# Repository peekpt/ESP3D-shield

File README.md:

## ESP3D-SHIELD
ESP3D - it's a software based on ESP8266 module to give Wi-Fi capabilities 3D Printers.

ESP3D-SHIELD - it's an adapter to connect a 3D printer AUX-1 port

--

*ESP3D info:*

* [ESP3D](https://github.com/luc-github/ESP3D)

* [ESP3D WEBUI](https://github.com/luc-github/ESP3D-WEBUI)

--

*WIP*

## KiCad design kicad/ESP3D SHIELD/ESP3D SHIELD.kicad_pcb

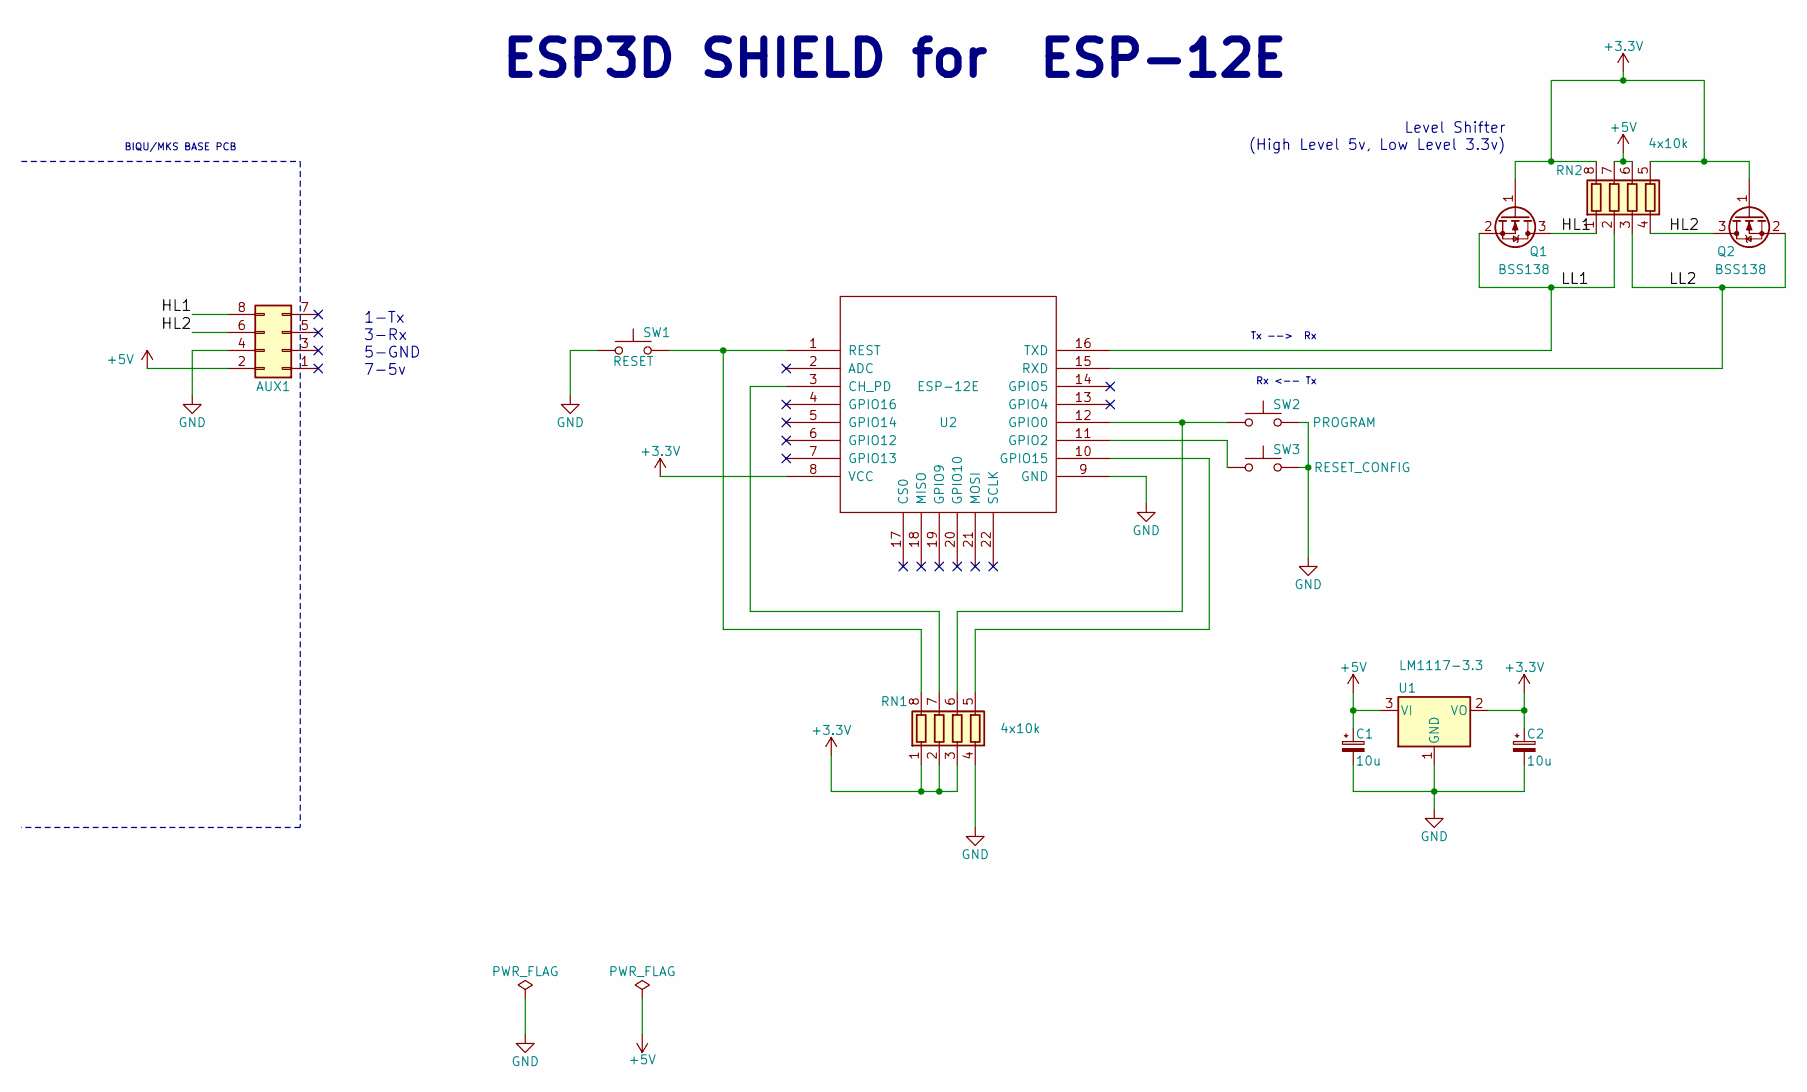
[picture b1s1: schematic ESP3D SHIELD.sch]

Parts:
AUX1: Conn_02x04_Odd_Even; Socket_Strip_Straight_2x04_Pitch2.54mm
C1, C2: 10u; CP_Tantalum_Case-A_EIA-3216-18_Reflow
Q1, Q2: BSS138; SOT-23
RN1, RN2: 4x10k; R_Array_Concave_4x0603
SW1: RESET; smd_push
SW2: PROGRAM; smd_push
SW3: RESET_CONFIG; smd_push
U1: LM1117-3.3; SOT-223
U2: ESP-12E; ESP-12E_SMD

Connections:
+3V3: C2.1, Q1.1 (G), Q2.1 (G), RN1.1 (R1.1), RN1.2 (R2.1), RN1.3 (R3.1), RN2.5 (R4.2), RN2.8 (R1.2), U1.2 (VO), U2.8 (VCC)
+5V: AUX1.2, C1.1, RN2.6 (R3.2), RN2.7 (R2.2), U1.3 (VI)
/HL1: AUX1.8, Q1.3 (D), RN2.1 (R1.1)
/HL2: AUX1.6, Q2.3 (D), RN2.4 (R4.1)
/LL1: Q1.2 (S), RN2.2 (R2.1), U2.16 (TXD)
/LL2: Q2.2 (S), RN2.3 (R3.1), U2.15 (RXD)
GND: AUX1.4, C1.2, C2.2, RN1.4 (R4.1), SW1.1, SW2.2, SW3.2, U1.1 (GND), U2.9 (GND)
unnamed: RN1.5 (R4.2), U2.10 (GPIO15)
unnamed: RN1.6 (R3.2), SW2.1, U2.12 (GPIO0)
unnamed: RN1.7 (R2.2), U2.3 (CH_PD)
unnamed: RN1.8 (R1.2), SW1.2, U2.1 (REST)
unnamed: SW3.1, U2.11 (GPIO2)

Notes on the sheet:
Level Shifter (High Level 5v, Low Level 3.3v)
1-Tx 3-Rx 5-GND 7-5v
BIQU/MKS BASE PCB
Tx --> Rx
Rx <-- Tx
ESP3D SHIELD for ESP-12E

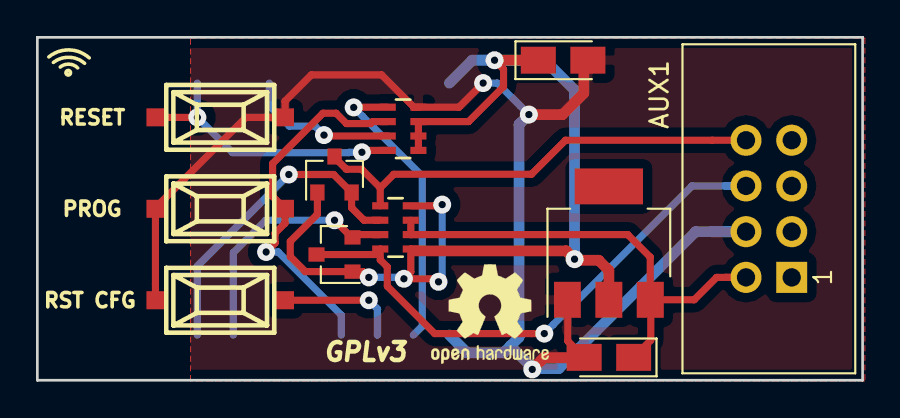
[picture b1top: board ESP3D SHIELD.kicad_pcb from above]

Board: 2 copper layers, 45.8 x 19.1 mm, 12 parts (1 on the bottom side), 12 nets.

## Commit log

2017-10-20 rev A
2017-10-20 connector is now IDC , bigger board
2017-10-20 revB final
2017-10-20 revB final2
2017-10-20 add some pics
2017-10-20 pics
2017-10-20 readme

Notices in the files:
kicad/ESP3D SHIELD/ESP3D SHIELD.kicad_pcb:
GPLv3
